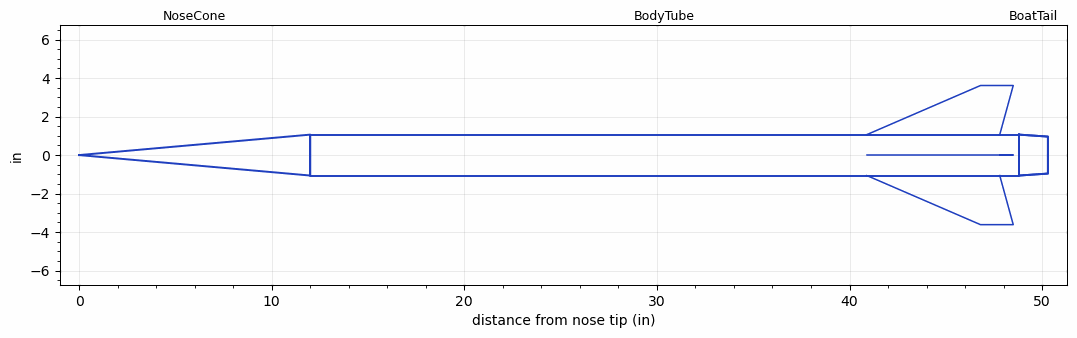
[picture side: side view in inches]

<RASAeroDocument>
 <FileVersion>2</FileVersion>
 <RocketDesign>
  <NoseCone>
   <Length>12</Length>
   <Diameter>2.125</Diameter>
   <Shape>Conical</Shape>
   <BluntRadius>0.05</BluntRadius>
   <Location>0</Location>
  </NoseCone>
  <BodyTube>
   <Length>36.8</Length>
   <Diameter>2.125</Diameter>
   <Location>12</Location>
   <BoattailLength>1.5</BoattailLength>
   <BoattailRearDiameter>1.92</BoattailRearDiameter>
   <Fin>
    <Count>4</Count>
    <Chord>6.9</Chord>
    <Span>2.55</Span>
    <SweepDistance>5.9</SweepDistance>
    <TipChord>1.7</TipChord>
    <Thickness>0.155</Thickness>
    <LERadius>0.005</LERadius>
    <Location>7.9</Location>
    <AirfoilSection>Hexagonal</AirfoilSection>
    <FX1>0.8</FX1>
    <FX3>0.5</FX3>
   </Fin>
  </BodyTube>
  <BoatTail>
   <Length>1.5</Length>
   <Diameter>2.125</Diameter>
   <RearDiameter>1.92</RearDiameter>
   <Location>48.8</Location>
  </BoatTail>
  <Surface>Camouflage Paint</Surface>
  <ModifiedBarrowman>True</ModifiedBarrowman>
  <Turbulence>True</Turbulence>
  <UseBooster1>False</UseBooster1>
  <UseBooster2>False</UseBooster2>
 </RocketDesign>
 <LaunchSite>
  <Altitude>4000</Altitude>
  <Pressure>0</Pressure>
  <RodAngle>2</RodAngle>
  <RodLength>7</RodLength>
  <Temperature>70</Temperature>
  <WindSpeed>4.47</WindSpeed>
 </LaunchSite>
 <Recovery>
  <Altitude1>656.168</Altitude1>
  <Altitude2>0</Altitude2>
  <DeviceType1>Parachute</DeviceType1>
  <DeviceType2>None</DeviceType2>
  <Event1>True</Event1>
  <Event2>False</Event2>
  <Size1>17.6</Size1>
  <Size2>0</Size2>
  <EventType1>Apogee</EventType1>
  <EventType2>None</EventType2>
  <CD1>0.8</CD1>
  <CD2>0</CD2>
 </Recovery>
 <SimulationList>
  <Simulation>
   <SustainerEngine>L2329  (teeb)</SustainerEngine>
   <SustainerLaunchWt>7.9</SustainerLaunchWt>
   <SustainerNozzleDiameter>1.75</SustainerNozzleDiameter>
   <SustainerCG>29.66</SustainerCG>
   <SustainerIgnitionDelay>0</SustainerIgnitionDelay>
   <Booster1SeparationDelay>0</Booster1SeparationDelay>
   <Booster1IgnitionDelay>0</Booster1IgnitionDelay>
   <IncludeBooster1>False</IncludeBooster1>
   <Booster2Delay>0</Booster2Delay>
   <IncludeBooster2>False</IncludeBooster2>
   <TimetoApogee>38.22959</TimetoApogee>
   <MaxAltitude>43726.75</MaxAltitude>
   <MaxVelocity>5421.977</MaxVelocity>
   <OptimumWt>9</OptimumWt>
   <OptimumMaxAlt>9</OptimumMaxAlt>
  </Simulation>
 </SimulationList>
</RASAeroDocument>
